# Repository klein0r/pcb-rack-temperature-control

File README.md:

# Rack Temperature Control

[Gerber-Files](https://github.com/klein0r/pcb-rack-temperature-control/releases)

## Preview

## License

The MIT License (MIT)

Copyright (c) 2026 Matthias Kleine <info@haus-automatisierung.com>

Permission is hereby granted, free of charge, to any person obtaining a copy
of this software and associated documentation files (the "Software"), to deal
in the Software without restriction, including without limitation the rights
to use, copy, modify, merge, publish, distribute, sublicense, and/or sell
copies of the Software, and to permit persons to whom the Software is
furnished to do so, subject to the following conditions:

The above copyright notice and this permission notice shall be included in
all copies or substantial portions of the Software.

THE SOFTWARE IS PROVIDED "AS IS", WITHOUT WARRANTY OF ANY KIND, EXPRESS OR
IMPLIED, INCLUDING BUT NOT LIMITED TO THE WARRANTIES OF MERCHANTABILITY,
FITNESS FOR A PARTICULAR PURPOSE AND NONINFRINGEMENT. IN NO EVENT SHALL THE
AUTHORS OR COPYRIGHT HOLDERS BE LIABLE FOR ANY CLAIM, DAMAGES OR OTHER
LIABILITY, WHETHER IN AN ACTION OF CONTRACT, TORT OR OTHERWISE, ARISING FROM,
OUT OF OR IN CONNECTION WITH THE SOFTWARE OR THE USE OR OTHER DEALINGS IN
THE SOFTWARE.

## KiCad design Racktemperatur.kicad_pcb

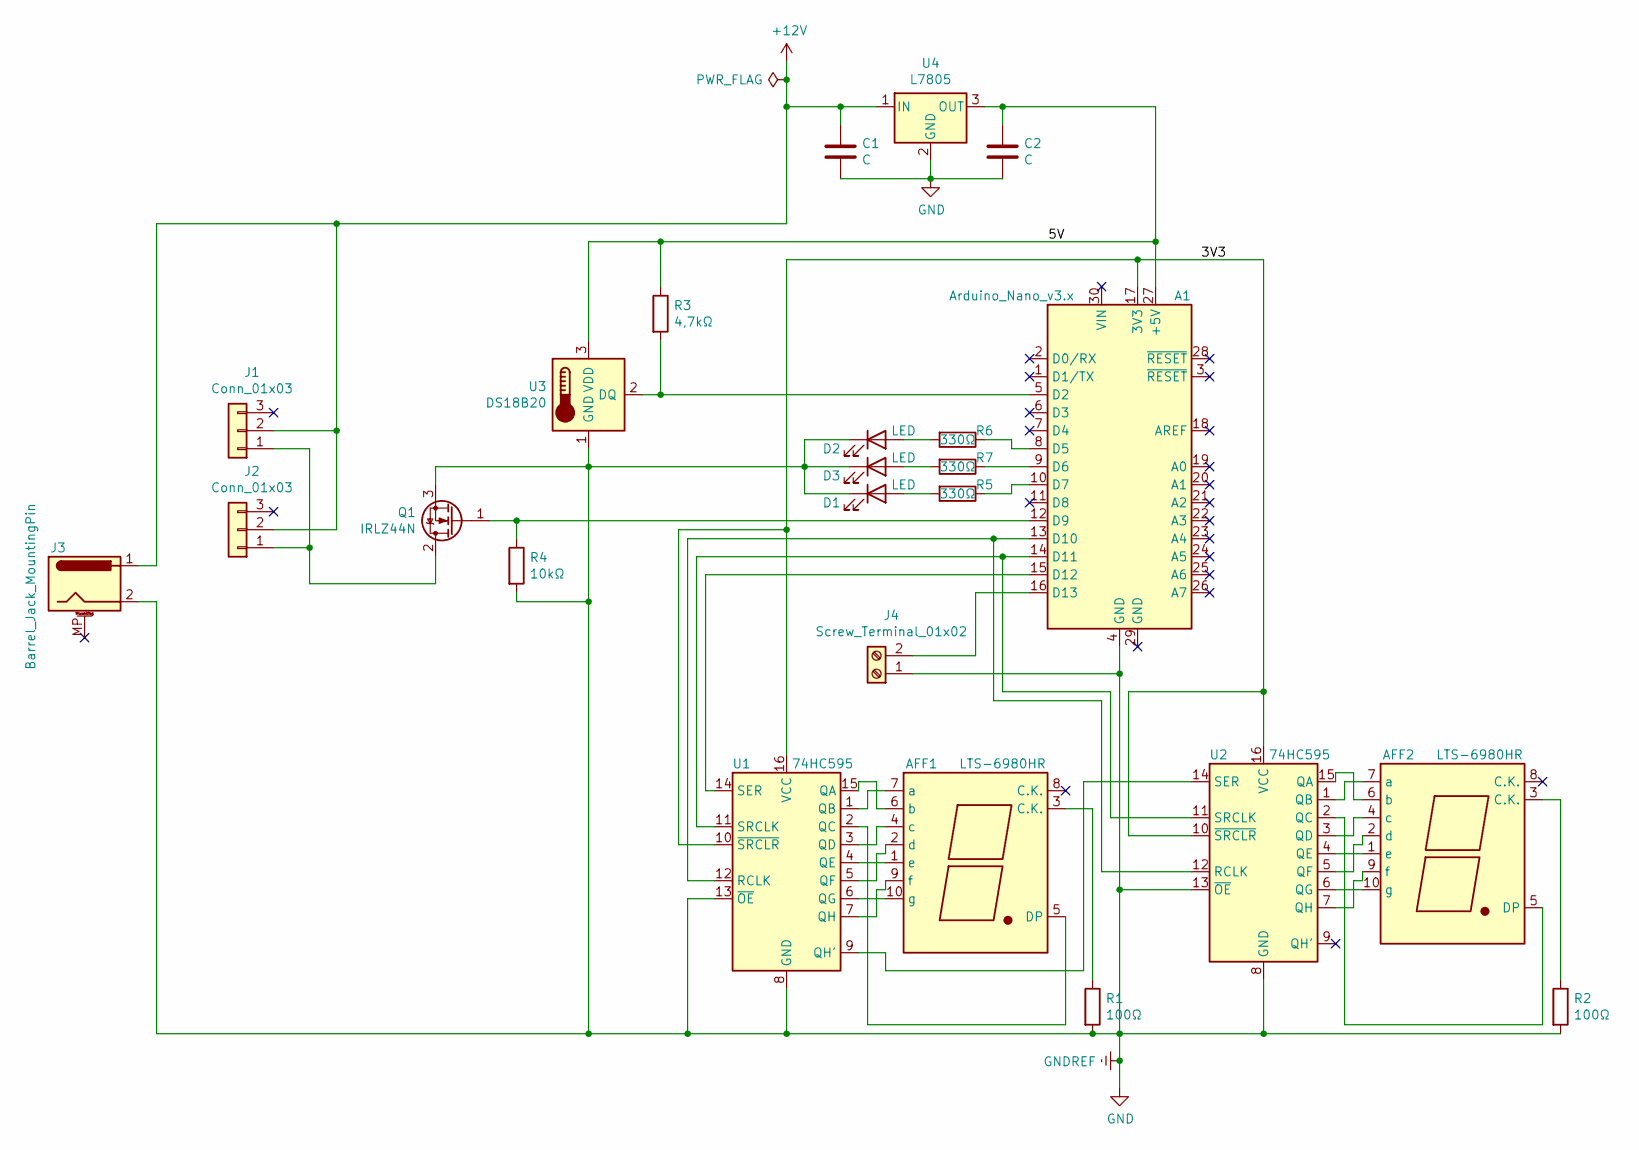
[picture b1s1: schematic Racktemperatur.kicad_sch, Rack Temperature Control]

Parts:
A1: Arduino_Nano_v3.x; Arduino_Nano_WithMountingHoles
AFF1, AFF2: LTS-6980HR; 7SegmentLED_LTS6760_LTS6780
C1, C2: C; C_0805_2012Metric_Pad1.18x1.45mm_HandSolder
D1, D2, D3: LED; LED_0805_2012Metric_Pad1.15x1.40mm_HandSolder
J1, J2: Conn_01x03; FanPinHeader_1x03_P2.54mm_Vertical
J3: Barrel_Jack_MountingPin; BarrelJack_Wuerth_6941xx301002
J4: Screw_Terminal_01x02; TerminalBlock_bornier-2_P5.08mm
Q1: IRLZ44N; TO-220-3_Horizontal_TabDown
R1, R2: 100Ω; R_0805_2012Metric_Pad1.20x1.40mm_HandSolder
R3: 4,7kΩ; R_0805_2012Metric_Pad1.20x1.40mm_HandSolder
R4: 10kΩ; R_0805_2012Metric_Pad1.20x1.40mm_HandSolder
R5, R6, R7: 330Ω; R_0805_2012Metric_Pad1.20x1.40mm_HandSolder
U1, U2: 74HC595; DIP-16_W7.62mm_LongPads
U3: DS18B20; TO-92_Inline
U4: L7805; TO-220-3_Horizontal_TabDown

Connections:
+12V: C1.1, J1.2, J2.2, J3.1, U4.1 (IN)
/3V3: A1.17 (3V3), U1.10 (~SRCLR), U1.16 (VCC), U2.10 (~SRCLR), U2.16 (VCC)
/5V: A1.27 (+5V), C2.1, R3.1, U3.3 (VDD), U4.3 (OUT)
GND: A1.4 (GND), C1.2, C2.2, D1.1 (K), D2.1 (K), D3.1 (K), J3.2, J4.1, Q1.3 (S), R1.2, R2.2, R4.2, U1.8 (GND), U1.13 (~OE), U2.8 (GND), U2.13 (~OE), U3.1 (GND), U4.2 (GND)
unnamed: A1.5 (D2), R3.2, U3.2 (DQ)
unnamed: A1.8 (D5), R6.1
unnamed: A1.9 (D6), R7.1
unnamed: A1.10 (D7), R5.1
unnamed: A1.12 (D9), Q1.1 (G), R4.1
unnamed: A1.13 (D10), U1.12 (RCLK), U2.12 (RCLK)
unnamed: A1.14 (D11), U1.11 (SRCLK), U2.11 (SRCLK)
unnamed: A1.15 (D12), U1.14 (SER)
unnamed: A1.16 (D13), J4.2
unnamed: AFF1.3 (C.K.), R1.1
unnamed: AFF1.5 (DP), U1.2 (QC)
unnamed: AFF1.7 (a), U1.1 (QB)
unnamed: AFF1.6 (b), U1.15 (QA)
unnamed: AFF1.4 (c), U1.3 (QD)
unnamed: AFF1.2 (d), U1.5 (QF)
unnamed: AFF1.1 (e), U1.4 (QE)
unnamed: AFF1.9 (f), U1.7 (QH)
unnamed: AFF1.10 (g), U1.6 (QG)
unnamed: AFF2.3 (C.K.), R2.1
unnamed: AFF2.5 (DP), U2.2 (QC)
unnamed: AFF2.7 (a), U2.1 (QB)
unnamed: AFF2.6 (b), U2.15 (QA)
unnamed: AFF2.4 (c), U2.3 (QD)
unnamed: AFF2.2 (d), U2.5 (QF)
unnamed: AFF2.1 (e), U2.4 (QE)
unnamed: AFF2.9 (f), U2.7 (QH)
unnamed: AFF2.10 (g), U2.6 (QG)
unnamed: D1.2 (A), R5.2
unnamed: D2.2 (A), R6.2
unnamed: D3.2 (A), R7.2
unnamed: J1.1, J2.1, Q1.2 (D)
unnamed: U1.9 (QH'), U2.14 (SER)

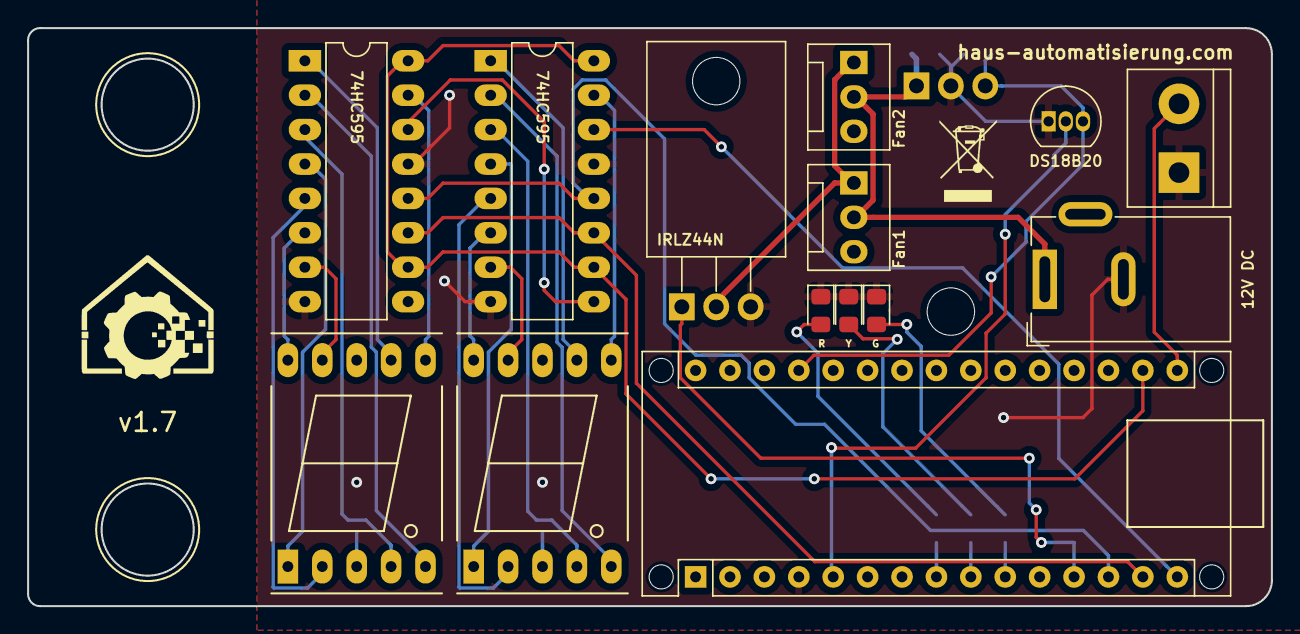
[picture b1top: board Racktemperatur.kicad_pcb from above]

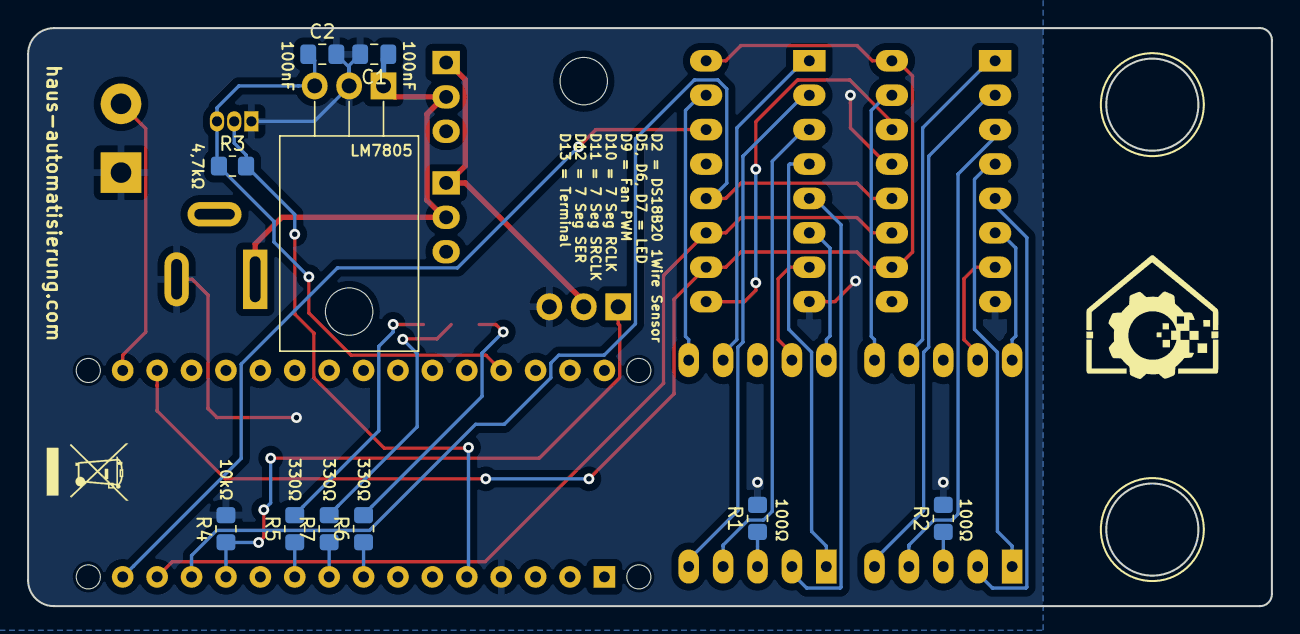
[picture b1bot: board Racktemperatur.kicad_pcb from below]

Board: 2 copper layers, 91.8 x 42.7 mm, 24 parts (10 on the bottom side), 36 nets.

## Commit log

2019-10-25 Version 1.3 as rack mount
2019-10-26 unconnected item
2019-10-26 Readme and License
2019-10-26 Removed DS Store
2019-10-26 Added LM7805
2019-11-12 Changed polarity of barrel jack
2019-11-12 Schema update
2019-11-12 Minor changes
2019-11-12 Updated preview
2020-11-22 Added Source Code
2020-11-22 Year 2020
2020-11-22 Added photo
2021-10-13 Preview Photo
2022-01-30 Update LICENSE
2022-01-31 Updated to KiCad 6
2024-03-15 v1.6
2024-05-06 v1.7
2025-07-03 Year 2025
2025-07-04 Updated PCB
2026-01-28 Year 2026
